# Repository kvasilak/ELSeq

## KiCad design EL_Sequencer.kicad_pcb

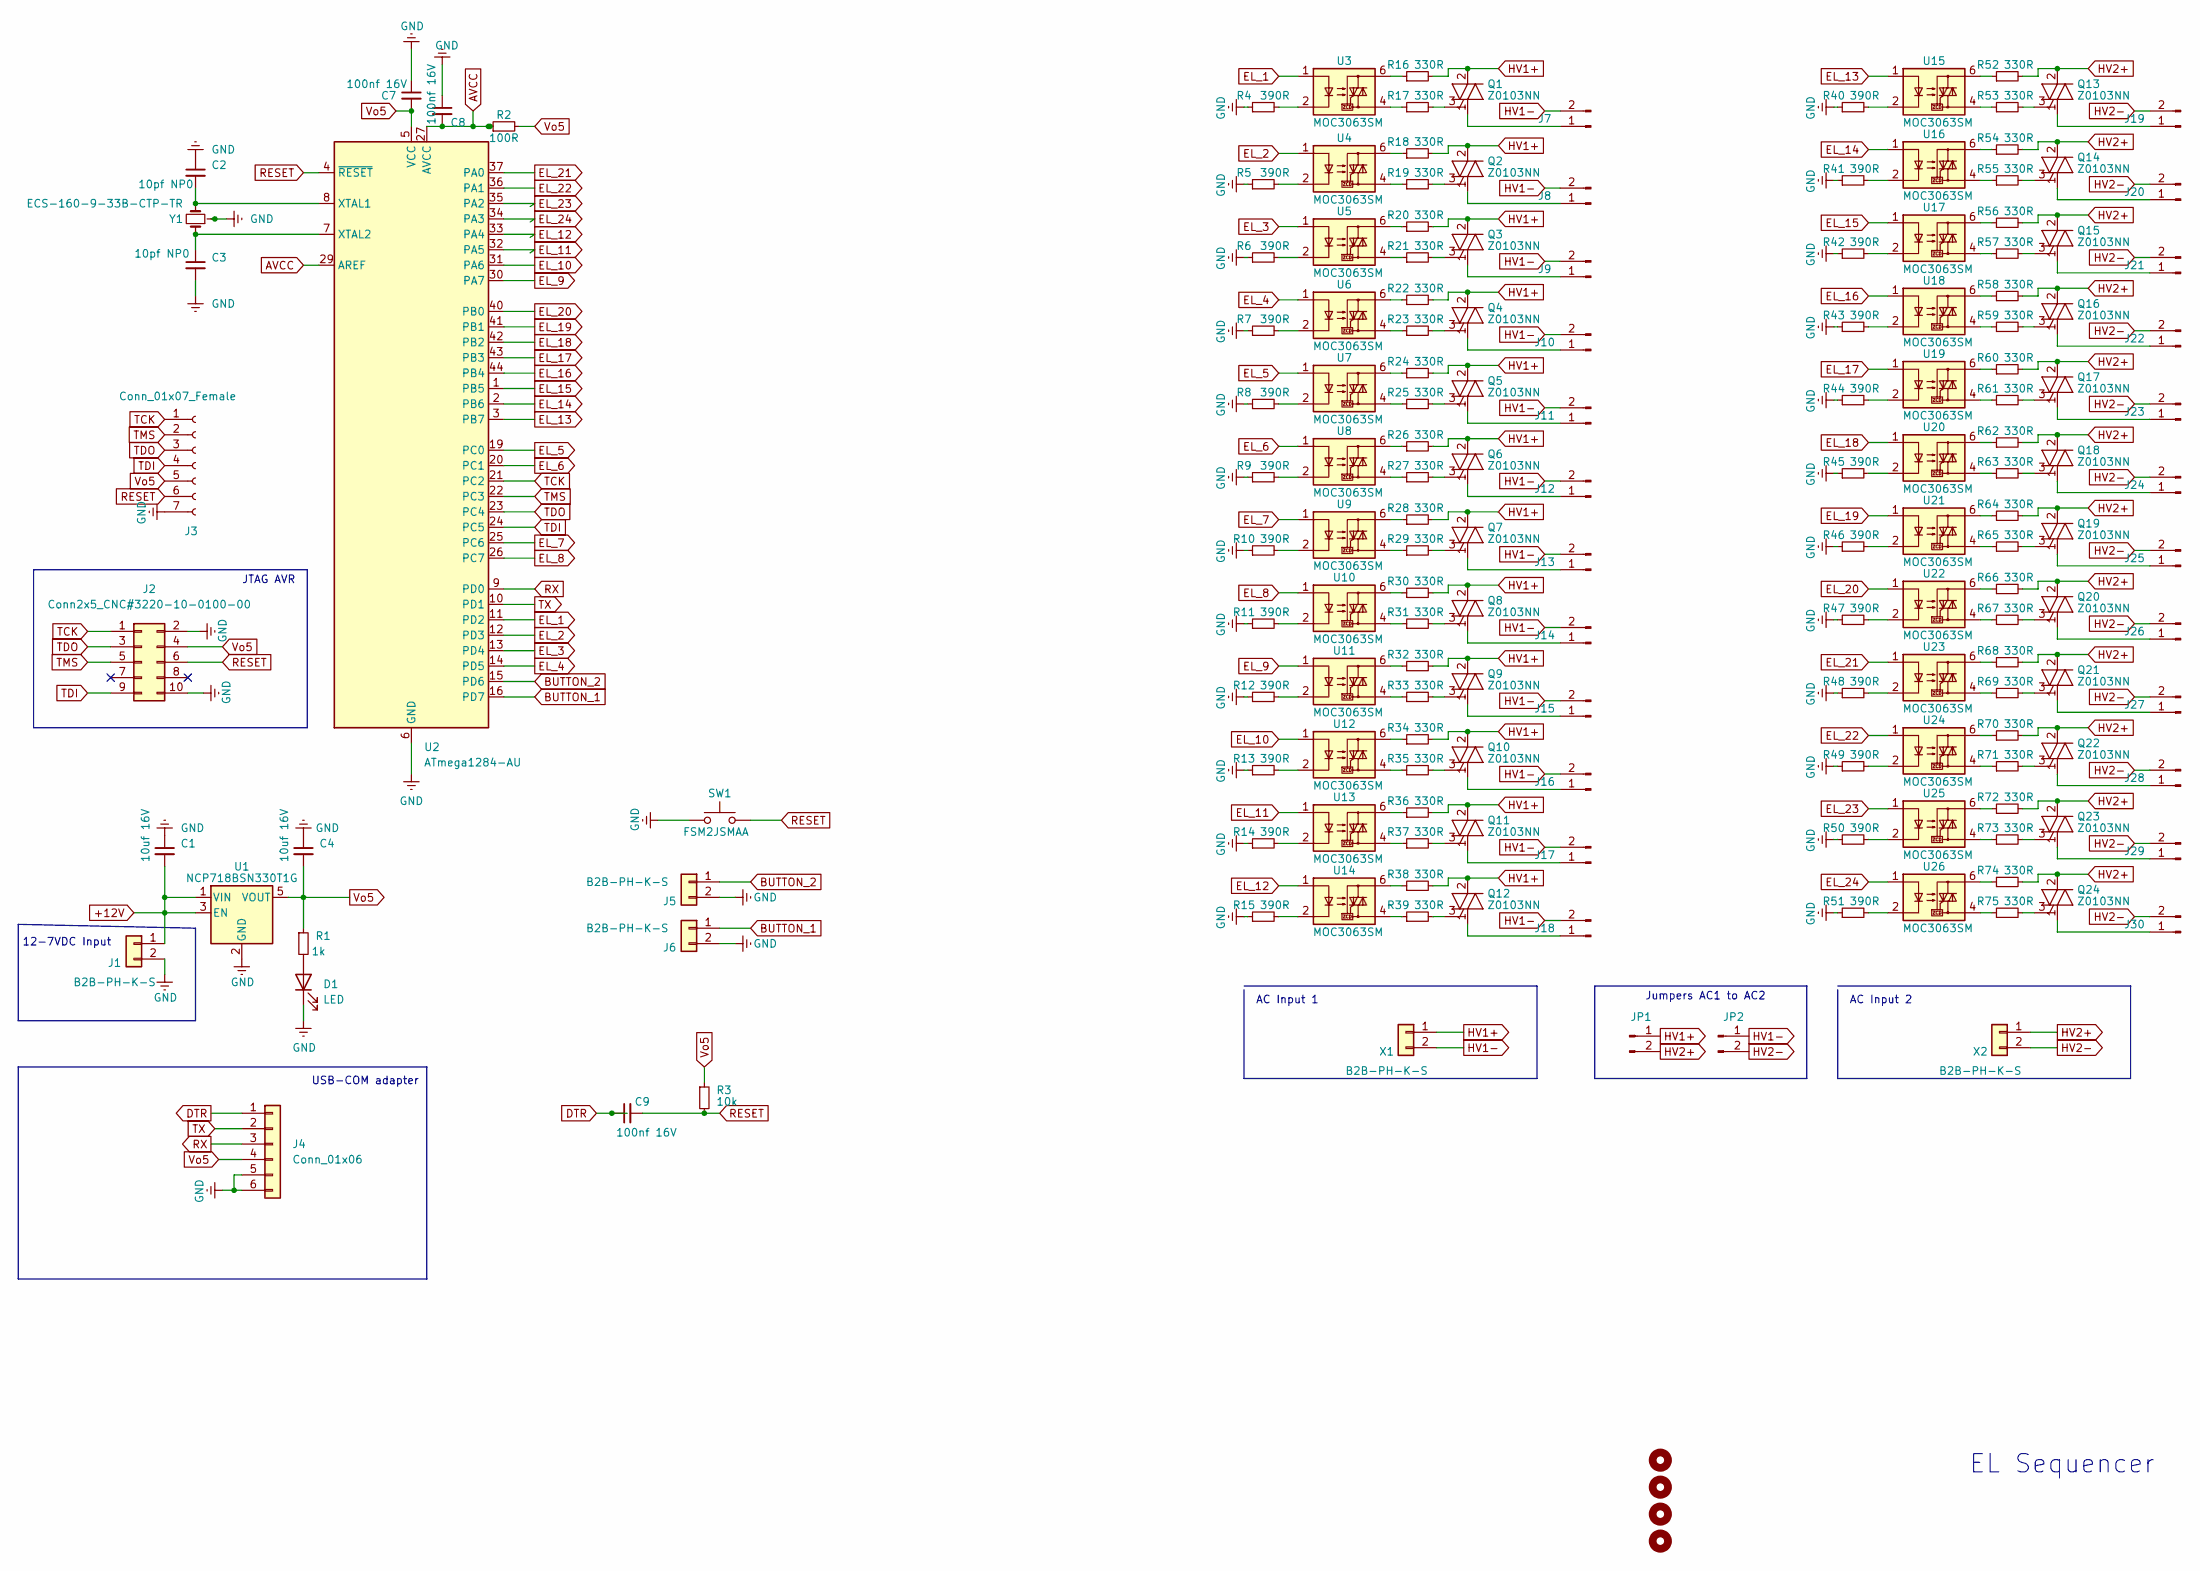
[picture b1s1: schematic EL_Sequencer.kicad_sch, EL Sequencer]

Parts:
C1, C4: 10uf 16V; C_0805_2012Metric
C2, C3: 10pf NP0; C_0805_2012Metric
C7, C8, C9: 100nf 16V; C_0805_2012Metric
D1: LED; LED_0805_2012Metric
H1, H2, H3, H4: MountingHole; MountingHole_3.2mm_M3
J1, J5, J6: B2B-PH-K-S; JST_PH_B2B-PH-K_1x02_P2.00mm_Vertical
J2: Conn2x5_CNC#3220-10-0100-00; PinSocket_2x05_P1.27mm_Vertical
J3: Conn_01x07_Female; PinHeader_1x07_P2.54mm_Vertical
J4: Conn_01x06; PinHeader_1x06_P2.54mm_Vertical
J7, J8, J9, J10, J11, J12, J13, J14, J15, J16, J17, J18, J19, J20, J21, J22, J23, J24, J25, J26, J27, J28, J29, J30: Header_01x02_Male; PinHeader_1x02_P2.54mm_Vertical
JP1, JP2: Header_01x02_Male; PinHeader_1x02_P2.54mm_Vertical
Q1: Z0103NN; SOT-223; LCSC C602954
Q2, Q3, Q4, Q5, Q6, Q7, Q8, Q9, Q10, Q11, Q12, Q13, Q14, Q15, Q16, Q17, Q18, Q19, Q20, Q21, Q22, Q23, Q24: Z0103NN; SOT-223
R1: 1k; R_0805_2012Metric
R2: 100R; R_0805_2012Metric
R3: 10k; R_0805_2012Metric
R4, R5, R6, R7, R8, R9, R10, R11, R12, R13, R14, R15, R40, R41, R42, R43, R44, R45, R46, R47, R48, R49, R50, R51: 390R; R_0805_2012Metric
R16, R17, R18, R19, R20, R21, R22, R23, R24, R25, R26, R27, R28, R29, R30, R31, R32, R33, R34, R35, R36, R37, R38, R39, R52, R53, R54, R55, R56, R57, R58, R59, R60, R61, R62, R63, R64, R65, R66, R67, R68, R69, R70, R71, R72, R73, R74, R75: 330R; R_0805_2012Metric
SW1: FSM2JSMAA; SW_Push_1P1T_NO_6x6mm_H5.0mm
U1: NCP718BSN330T1G; SOT-23-5; LCSC C892795
U2: ATmega1284-AU; TQFP-44_10x10mm_P0.8mm; LCSC C33575
U3: MOC3063SM; SMDIP-6_W9.53mm; LCSC C77950
U4, U5, U6, U7, U8, U9, U10, U11, U12, U13, U14, U15, U16, U17, U18, U19, U20, U21, U22, U23, U24, U25, U26: MOC3063SM; SMDIP-6_W9.53mm
X1, X2: B2B-PH-K-S; JST_PH_B2B-PH-K_1x02_P2.00mm_Vertical
Y1: ECS-160-9-33B-CTP-TR; Crystal_SMD_3225-4Pin_3.2x2.5mm

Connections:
+12V: C1.2, J1.1, U1.1 (VIN), U1.3 (EN)
AVCC: C8.2, R2.1, U2.27 (AVCC), U2.29 (AREF)
BUTTON_1: J6.1, U2.16 (PD7)
BUTTON_2: J5.1, U2.15 (PD6)
DTR: C9.1, J4.1
EL_1: U2.11 (PD2), U3.1
EL_2: U2.12 (PD3), U4.1
EL_3: U2.13 (PD4), U5.1
EL_4: U2.14 (PD5), U6.1
EL_5: U2.19 (PC0), U7.1
EL_6: U2.20 (PC1), U8.1
EL_7: U2.25 (PC6), U9.1
EL_8: U2.26 (PC7), U10.1
EL_9: U2.30 (PA7), U11.1
EL_10: U2.31 (PA6), U12.1
EL_11: U2.32 (PA5), U13.1
EL_12: U2.33 (PA4), U14.1
EL_13: U2.3 (PB7), U15.1
EL_14: U2.2 (PB6), U16.1
EL_15: U2.1 (PB5), U17.1
EL_16: U2.44 (PB4), U18.1
EL_17: U2.43 (PB3), U19.1
EL_18: U2.42 (PB2), U20.1
EL_19: U2.41 (PB1), U21.1
EL_20: U2.40 (PB0), U22.1
EL_21: U2.37 (PA0), U23.1
EL_22: U2.36 (PA1), U24.1
EL_23: U2.35 (PA2), U25.1
EL_24: U2.34 (PA3), U26.1
GND: C1.1, C2.1, C3.2, C4.1, C7.1, C8.1, D1.1 (K), J1.2, J2.2, J2.10, J3.7, J4.5, J4.6, J5.2, J6.2, R4.1, R5.1, R6.1, R7.1, R8.1, R9.1, R10.1, R11.1, R12.1, R13.1, R14.1, R15.1, R40.1, R41.1, R42.1, R43.1, R44.1, R45.1, R46.1, R47.1, R48.1, R49.1, R50.1, R51.1, SW1.3 (B), SW1.4 (B), U1.2 (GND), U2.6 (GND), U2.18 (GND), U2.28 (GND), U2.39 (GND), Y1.2 (GND), Y1.4 (GND); also elsewhere on the board
HV1+: JP1.1, Q1.2 (A2), Q1.4 (A4), Q2.2 (A2), Q2.4 (A4), Q3.2 (A2), Q3.4 (A4), Q4.2 (A2), Q4.4 (A4), Q5.2 (A2), Q5.4 (A4), Q6.2 (A2), Q6.4 (A4), Q7.2 (A2), Q7.4 (A4), Q8.2 (A2), Q8.4 (A4), Q9.2 (A2), Q9.4 (A4), Q10.2 (A2), Q10.4 (A4), Q11.2 (A2), Q11.4 (A4), Q12.2 (A2), Q12.4 (A4), R16.2, R18.2, R20.2, R22.2, R24.2, R26.2, R28.2, R30.2, R32.2, R34.2, R36.2, R38.2, X1.1
HV1-: J7.2, J8.2, J9.2, J10.2, J11.2, J12.2, J13.2, J14.2, J15.2, J16.2, J17.2, J18.2, JP2.1, X1.2
HV2+: JP1.2, Q13.2 (A2), Q13.4 (A4), Q14.2 (A2), Q14.4 (A4), Q15.2 (A2), Q15.4 (A4), Q16.2 (A2), Q16.4 (A4), Q17.2 (A2), Q17.4 (A4), Q18.2 (A2), Q18.4 (A4), Q19.2 (A2), Q19.4 (A4), Q20.2 (A2), Q20.4 (A4), Q21.2 (A2), Q21.4 (A4), Q22.2 (A2), Q22.4 (A4), Q23.2 (A2), Q23.4 (A4), Q24.2 (A2), Q24.4 (A4), R52.2, R54.2, R56.2, R58.2, R60.2, R62.2, R64.2, R66.2, R68.2, R70.2, R72.2, R74.2, X2.1
HV2-: J19.2, J20.2, J21.2, J22.2, J23.2, J24.2, J25.2, J26.2, J27.2, J28.2, J29.2, J30.2, JP2.2, X2.2
unnamed: D1.2 (A), R1.2
unnamed: J7.1, Q1.1 (A1)
unnamed: J8.1, Q2.1 (A1)
unnamed: J9.1, Q3.1 (A1)
unnamed: J10.1, Q4.1 (A1)
unnamed: J11.1, Q5.1 (A1)
unnamed: J12.1, Q6.1 (A1)
unnamed: J13.1, Q7.1 (A1)
unnamed: J14.1, Q8.1 (A1)
unnamed: J15.1, Q9.1 (A1)
unnamed: J16.1, Q10.1 (A1)
unnamed: J17.1, Q11.1 (A1)
unnamed: J18.1, Q12.1 (A1)
unnamed: J19.1, Q13.1 (A1)
unnamed: J20.1, Q14.1 (A1)
unnamed: J21.1, Q15.1 (A1)
unnamed: J22.1, Q16.1 (A1)
unnamed: J23.1, Q17.1 (A1)
unnamed: J24.1, Q18.1 (A1)
unnamed: J25.1, Q19.1 (A1)
unnamed: J26.1, Q20.1 (A1)
unnamed: J27.1, Q21.1 (A1)
unnamed: J28.1, Q22.1 (A1)
unnamed: J29.1, Q23.1 (A1)
unnamed: J30.1, Q24.1 (A1)
unnamed: Q1.3 (G), R17.2
unnamed: Q2.3 (G), R19.2
unnamed: Q3.3 (G), R21.2
unnamed: Q4.3 (G), R23.2
unnamed: Q5.3 (G), R25.2
unnamed: Q6.3 (G), R27.2
unnamed: Q7.3 (G), R29.2
unnamed: Q8.3 (G), R31.2
unnamed: Q9.3 (G), R33.2
unnamed: Q10.3 (G), R35.2
unnamed: Q11.3 (G), R37.2
unnamed: Q12.3 (G), R39.2
unnamed: Q13.3 (G), R53.2
unnamed: Q14.3 (G), R55.2
unnamed: Q15.3 (G), R57.2
unnamed: Q16.3 (G), R59.2
unnamed: Q17.3 (G), R61.2
unnamed: Q18.3 (G), R63.2
unnamed: Q19.3 (G), R65.2
unnamed: Q20.3 (G), R67.2
unnamed: Q21.3 (G), R69.2
unnamed: Q22.3 (G), R71.2
unnamed: Q23.3 (G), R73.2
unnamed: Q24.3 (G), R75.2
unnamed: R4.2, U3.2
unnamed: R5.2, U4.2
unnamed: R6.2, U5.2
unnamed: R7.2, U6.2
unnamed: R8.2, U7.2
unnamed: R9.2, U8.2
unnamed: R10.2, U9.2
unnamed: R11.2, U10.2
unnamed: R12.2, U11.2
unnamed: R13.2, U12.2
unnamed: R14.2, U13.2
unnamed: R15.2, U14.2
unnamed: R16.1, U3.6
unnamed: R17.1, U3.4
unnamed: R18.1, U4.6
unnamed: R19.1, U4.4
unnamed: R20.1, U5.6
unnamed: R21.1, U5.4
unnamed: R22.1, U6.6
unnamed: R23.1, U6.4
unnamed: R24.1, U7.6
unnamed: R25.1, U7.4
unnamed: R26.1, U8.6
unnamed: R27.1, U8.4
unnamed: R28.1, U9.6
unnamed: R29.1, U9.4
unnamed: R30.1, U10.6
unnamed: R31.1, U10.4
unnamed: R32.1, U11.6
unnamed: R33.1, U11.4
unnamed: R34.1, U12.6
unnamed: R35.1, U12.4
unnamed: R36.1, U13.6
unnamed: R37.1, U13.4
unnamed: R38.1, U14.6
unnamed: R39.1, U14.4
unnamed: R40.2, U15.2
unnamed: R41.2, U16.2
unnamed: R42.2, U17.2
unnamed: R43.2, U18.2
unnamed: R44.2, U19.2
unnamed: R45.2, U20.2
unnamed: R46.2, U21.2
unnamed: R47.2, U22.2
unnamed: R48.2, U23.2
unnamed: R49.2, U24.2
unnamed: R50.2, U25.2
unnamed: R51.2, U26.2
unnamed: R52.1, U15.6
unnamed: R53.1, U15.4
unnamed: R54.1, U16.6
unnamed: R55.1, U16.4
unnamed: R56.1, U17.6
unnamed: R57.1, U17.4
unnamed: R58.1, U18.6
unnamed: R59.1, U18.4
unnamed: R60.1, U19.6
unnamed: R61.1, U19.4
unnamed: R62.1, U20.6
unnamed: R63.1, U20.4
unnamed: R64.1, U21.6
unnamed: R65.1, U21.4
unnamed: R66.1, U22.6
unnamed: R67.1, U22.4
unnamed: R68.1, U23.6
unnamed: R69.1, U23.4
unnamed: R70.1, U24.6
unnamed: R71.1, U24.4
unnamed: R72.1, U25.6
unnamed: R73.1, U25.4
unnamed: R74.1, U26.6
unnamed: R75.1, U26.4
unnamed: C3.1, U2.7 (XTAL2), Y1.1
unnamed: C2.2, U2.8 (XTAL1), Y1.3
RESET: C9.2, J2.6, J3.6, R3.2, SW1.1 (A), SW1.2 (A), U2.4 (~RESET)
RX: J4.3, U2.9 (PD0)
TCK: J2.1, J3.1, U2.21 (PC2)
TDI: J2.9, J3.4, U2.24 (PC5)
TDO: J2.3, J3.3, U2.23 (PC4)
TMS: J2.5, J3.2, U2.22 (PC3)
TX: J4.2, U2.10 (PD1)
Vo5: C4.2, C7.2, J2.4, J3.5, J4.4, R1.1, R2.2, R3.1, U1.5 (VOUT), U2.5 (VCC), U2.17 (VCC), U2.38 (VCC); also elsewhere on the board

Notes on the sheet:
Jumpers AC1 to AC2
12-7VDC Input
AC Input 2
EL Sequencer
JTAG AVR
USB-COM adapter
AC Input 1

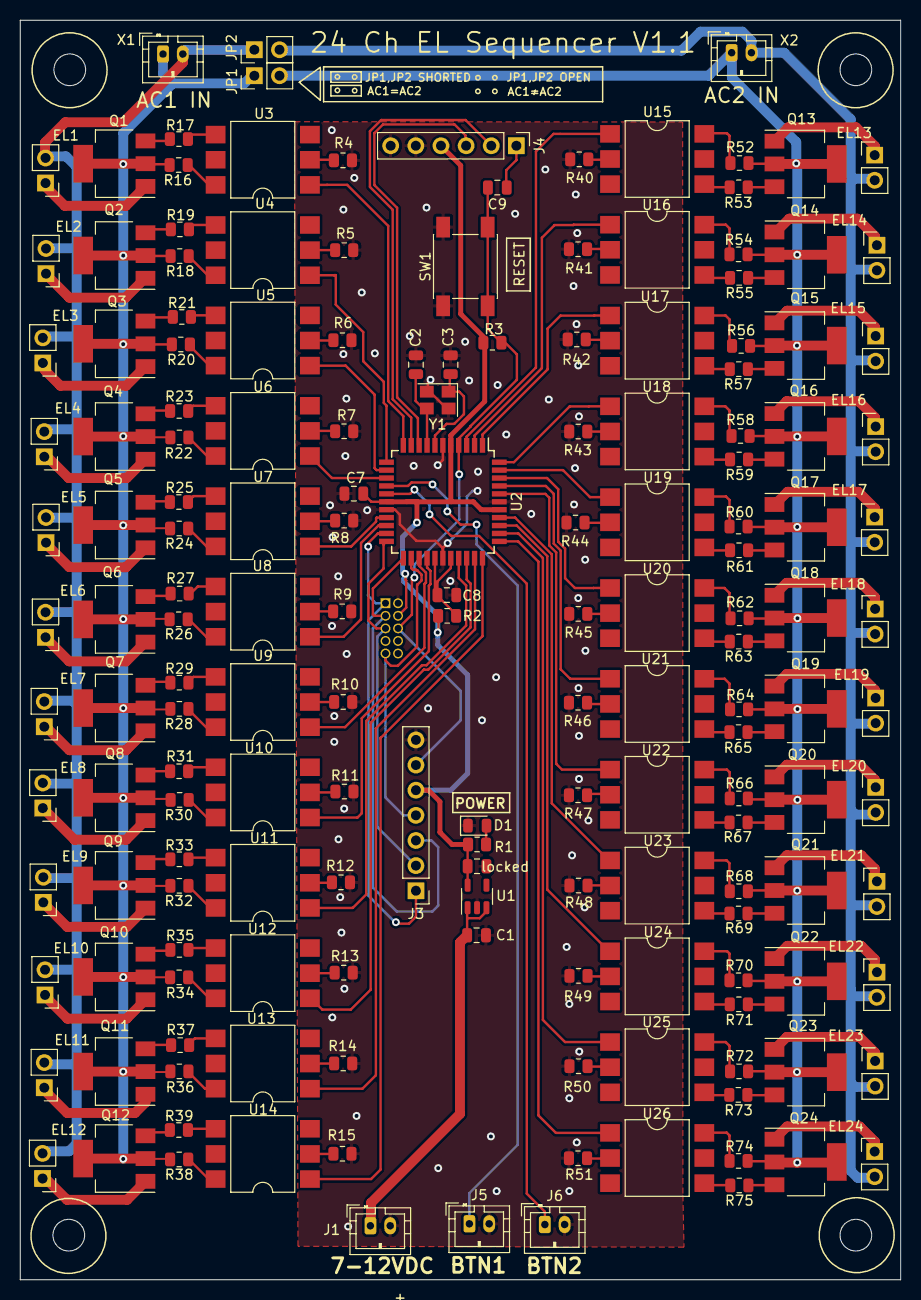
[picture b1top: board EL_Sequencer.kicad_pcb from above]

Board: 2 copper layers, 89.0 x 127.2 mm, 173 parts (1 on the bottom side), 165 nets.

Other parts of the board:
locked: 10uf 16V; C_0805_2012Metric

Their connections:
GND: locked.1; also elsewhere on the board
Vo5: locked.2; also elsewhere on the board

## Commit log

2023-03-12 Arduino compatible and smaller

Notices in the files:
EL_Sequencer.kicad_pcb:
Corvette Engineering © 2023
